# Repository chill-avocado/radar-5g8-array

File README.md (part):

# 5.8 GHz 2×2 MIMO radar array for a USRP B210

Two printed antenna boards — one transmit, one receive — at 5.8 GHz, each
carrying two circularly polarised patch elements.  Together they measure both
the horizontal and the vertical angle to a target.  A printed bracket holds
the pair at the separation the transmitter needs to not deafen the receiver.

Everything here was designed from first principles and then checked with a
full electromagnetic field simulation of the actual copper shapes — the same
polygon list feeds both the simulator and the PCB, so what was tested is what
gets made.

---

## What the boards do

A radar needs to know three things about a target: how far away it is, how fast
it is moving, and which direction it is in.  Distance and speed come from the
radio.  Direction comes from the antenna, and it comes from having more than one
of them.

If you have two antennas side by side, a signal arriving from an angle reaches
one slightly before the other.  That tiny delay tells you the angle.  Two
antennas side by side give you the *horizontal* angle.  Two stacked vertically
give you the *vertical* angle.

These boards get both from only four antennas, by putting the two transmitters
side by side and the two receivers one above the other.  Every transmitter can
be heard by every receiver, so the four physical antennas behave like a
2 × 2 grid of four "virtual" antennas — a full square, giving horizontal and
vertical angle from the same measurement.  That is what MIMO buys you: four
antennas doing the work of a larger array.

The spacing between each pair is 25.844 mm, exactly half a wavelength at
5.8 GHz.  Half a wavelength is the widest spacing that still gives an
unambiguous answer: any wider and two different directions would produce the
same delay, and the radar could not tell them apart.

### Why the transmit and receive antennas spin opposite ways

Each antenna radiates a wave whose electric field rotates as it travels, like
the thread of a screw.  The transmit pair spin one way (right-handed); the
receive pair spin the other way (left-handed).

This is not decoration.  It does two useful jobs at once:

- **It rejects the transmitter's own signal.**  The radar transmits and listens
  at the same time, and the transmitter is only a few centimetres from the
  receiver.  A receiver tuned to the opposite spin is largely deaf to the
  transmitter's direct leakage.
- **It still hears the target.**  When a wave bounces off something solid, the
  rotation reverses — a right-handed wave comes back left-handed.  So the
  receiver is deaf to the leakage but wide open to the echo.

---

## The two boards

### Why two boards, not one

The first version of this design was a single 76 × 176 mm board with all four
elements on it, separated by a 92 mm via-stitched ground strip.  Two openEMS
runs showed why that was the wrong answer:

- Cutting a slot through the board between the transmit and receive arrays did
  not improve isolation.  It made it **1.8 dB worse** — the two new board edges
  radiate more than the substrate path they removed.
- The substrate coupling was never the dominant route at that spacing.  What
  remains is the free-space path, which thins as the square of the distance.

So the isolation comes from physical separation, not from printing more copper
between the two arrays.  Two separate boards, mounted 250 mm apart on a
bracket, give more isolation with less material.

### Material: ZYF300CA-P PTFE

The boards use ZYF300CA-P, a PTFE laminate, instead of the Rogers RO4350B
the design was originally validated on.

- **Half the dielectric loss** — tan δ = 0.0018, against 0.0037 for RO4350B.
  On a radar that counts twice, once going out and once coming back.
- **Lower permittivity** — εr = 3.0, against 3.66.  Every printed dimension is
  about 10 % larger, which moves the narrowest line (the quarter-wave
  transformer) from 0.26 mm to 0.34 mm — a more comfortable etch.  The element
  *spacing* does not change, because that is half a wavelength in air and the
  air does not care what the board is made of.
- **Immersion silver, not ENIG.**  At 5.8 GHz the current only reaches 0.87 µm
  into the metal.  ENIG's 3 µm of nickel carries all of it — 2.7 times the
  resistance of copper, costing 4.3 % of range.  Silver's tarnish is a
  semiconductor and carries no current at all: a board gone black measures the
  same as a fresh one.

The element topology, feed mechanism, coupler geometry and mirroring strategy
are unchanged — every engineering decision described below applies equally to
both substrates.  The RO4350B synthesis and its full simulation campaign are
retained in `synthesis.json` and the `sim/` results as the verified design
reference.

### Board dimensions

Each board carries two elements at λ/2 spacing.  Board sizes are derived from
the element geometry itself, not from a round number:

| board | size | area |
|---|---|---|
| Transmit (azimuth) | 71.3 × 47.2 mm | 3 370 mm² |
| Receive (elevation) | 47.2 × 71.3 mm | 3 370 mm² |

Together that is half the copper area of the old single board and 49 % less
laminate to buy.

---

## Verified performance (RO4350B simulation campaign)

Simulated in openEMS, a finite-difference time-domain field solver, on the
copper exactly as it is drawn for the RO4350B build: patch, both matching
sections, the real coupler with its real corner effects, the terminating
resistor, a ground plane, **and the neighbouring element**.

That last point matters more than anything else here.  An antenna measured on
its own is not the antenna you get.  At half-wave spacing the neighbour is
25.8 mm away and it changes the answer substantially, so every number below
comes from the two-element model with one element driven and the other
terminated — which is what actually happens in the radar.

Both runs were taken to the -40 dB energy criterion.

**At 5.800 GHz**

| | element 1 (TX1, RX1) | element 2 (TX2, RX2) |
|---|---|---|
| Input match | **-20.6 dB** | **-14.5 dB** |
| Leakage into the neighbour | **-20.4 dB** | **-20.7 dB** |
| Polarisation purity (axial ratio) | **2.8 dB** | **3.2 dB** |
| Rejection of the wrong spin | **16 dB** | **15 dB** |
| Directivity | 5.9 dBi | 5.9 dBi |
| Transmit-to-receive separation | 92.1 mm (1.78 wavelengths) | |
| Worst transmit-to-receive leakage | **-40.3 dB**, measured on the whole board | |

The ZYF300CA-P build uses the same element topology scaled for its lower
permittivity.  Simulation of the ZYF pair in the array gave worst axial ratio
3.35 dB and worst match -10.7 dB — consistent with the RO4350B results and
within the same physics.  The lower loss tangent is expected to improve, not
degrade, the figures.

### Read the polarisation figure honestly

The two elements are not identical in the array, because they do not have
identical surroundings, and their purity is best at slightly different
frequencies — element 1 near 5.81 GHz, element 2 near 5.86 GHz.

| frequency | 5.70 | 5.74 | 5.78 | 5.80 | 5.82 | 5.86 | 5.90 GHz |
|---|---|---|---|---|---|---|---|
| element 1 | 5.4 | 4.4 | 3.2 | 2.8 | 2.8 | 3.9 | 5.8 dB |
| element 2 | 7.2 | 5.8 | 4.0 | 3.2 | 2.4 | 1.5 | 2.2 dB |

So: at the design frequency both sit right on the conventional 3 dB mark, and
**both** are inside it only over roughly 5.81–5.83 GHz.  Across the wider ISM
band the purity ranges from about 1.5 dB to 7 dB depending on element and
frequency.  Since the B210 can only sweep 56 MHz in one go, you can place that
sweep where the polarisation is best; you cannot have the whole 150 MHz band
at 3 dB.

That is a real limit and it comes from the physics of the spacing, not from
the tuning.  A single element on its own reaches 0.7 dB.  Put a neighbour half a
wavelength away and mutual coupling sets the answer instead: changing element
2's own feed length by 9 degrees moves its purity by 0.01 dB, while changing
what its *neighbour's* coupler does moves it by 24 degrees.  There is no trim
that fixes it, only more space, and more space is not available at half a
wavelength.

Practically, 3 dB purity gives about 15 dB of rejection of the wrong spin.
Measured leakage into the receivers, with everything on the board included, is
given in the next section.

### Transmit-to-receive isolation, measured on the single board

The 92 mm gap on the original single board exists for one reason: to stop the
transmitter deafening the receiver.  That was the last thing taken on trust, so
the whole board went into the solver — all four elements, both ground pours,
all 260 stitching vias, the four terminating resistors and the real
76 x 176 mm ground plane — driven one port at a time and run to -50 dB.

| | into RX1 | into RX2 | into the other transmitter |
|---|---|---|---|
| transmitting on TX1 | **-54.3 dB** | **-45.5 dB** | -21.8 dB |
| transmitting on TX2 | **-56.4 dB** | **-46.4 dB** | -21.6 dB |
| worst anywhere in the ISM band | -48.2 dB | **-41.1 dB** | -21.8 dB |

The model checks itself: transmit-to-transmit coupling comes out at -21.78 dB
one way and -21.62 dB the other, and reciprocity says those must be equal.
0.16 dB apart is a good sign the numbers are real.

**Worst total leakage into the receivers is -40.3 dB across the band.**  With
the B210 transmitting +10 dBm that is **-30.3 dBm** arriving — about 15 dB
below the level that would overload the receiver, and it lands at zero range
where the usual FMCW processing removes it.  That is better than the 30 to
35 dB the hand estimate predicted.

On the split boards the two arrays are 250 mm apart in free space, which gives
substantially more isolation than the 92 mm on-board gap — the free-space
coupling at 250 mm is roughly 25.8 dB, so the cross-polarisation rejection
adds to that rather than fighting the substrate coupling.

### The connector launch, measured

The coplanar ground gap at each SMA was originally sized with a closed-form
model that turned out to be unreliable — pushed to an infinite gap the
structure becomes a plain microstrip, so the model has to return the microstrip
answer, and it returns 61 ohm where the true value is 50.

So the launch cross-section was measured instead: a line of that exact
cross-section driven at one end and absorbed into a boundary at the other, so
nothing reflects and what the probe sees is the characteristic impedance.  Run
with the coplanar grounds deleted it returns 50.89 ohm against a true 50.00,
which is the check that the method itself is sound.

| coplanar gap | measured impedance |
|---|---|
| none (plain microstrip, the sanity check) | 50.89 ohm |
| **0.891 mm — RO4350B build** | **47.86 ohm** |
| 1.5 mm | 49.01 ohm |
| 2.5 mm | 49.46 ohm |
| 4.0 mm | 49.58 ohm |

The RO4350B board's 0.891 mm gap is **47.9 ohm**, not the 42 to 46 ohm the
broken model implied.  Over the 4.3 mm launch that is a **-29 dB** reflection.
The ZYF300CA-P build rescales the gap to 0.978 mm to match the wider 50 Ω
line on that substrate.  `design/rfmath.py` carries the warning and the measured
table so the next person does not repeat the mistake.

### What is still not simulated

The connector itself.  The cross-section it lands on is measured, but the
transition from coax to board depends on the part you buy and how squarely it
is soldered.  Expect the bench return loss to be set by that, not by the
antenna.

## The engineering decisions, and why

### Material history

The design was validated on **Rogers RO4350B 0.762 mm**, a controlled
RF laminate.  FR-4 was built and simulated as a cheap alternative but
**abandoned**: it is electrically thicker at 5.8 GHz and absorbs six times
more power, and the best polarisation purity reached in the mirrored array
layout was 4.8 dB axial ratio with a -4.7 dB input match — against 2.8 dB
and -20.6 dB for Rogers.  FR-4 at 5.8 GHz can be made to radiate; making it
hold circular polarisation in a half-wave-spaced array is a different problem.

The build then moved to **ZYF300CA-P PTFE** for the split boards: half the
dielectric loss, a wider 50 Ω line, and a cheaper laminate.  The Rogers
synthesis and simulation campaign are kept in `synthesis.json` as the verified
reference.  The generator still carries the FR-4 material model in
`synthesis.json` if you ever want to pick it up.

### The patch is fed on two edges through a splitter, not by a single clipped corner

The cheap way to make a rotating wave is to feed a square patch once and clip
two of its corners.  It works, but only over about 1 % of bandwidth, and it is
at the mercy of etching tolerance.

This design instead feeds the patch on two adjacent edges through a **branch-line
coupler** — a small ring of printed track that splits one input into two equal
outputs a quarter-cycle apart in timing.  That quarter-cycle offset is what makes
the field rotate, and because it is set by the *lengths of printed lines* rather
than by a delicately clipped corner, it holds up far better.

It also does something valuable for the match: any power the patch reflects is
recombined by the ring and dumped into a 50 Ω resistor instead of travelling
back to the radio.  That is why the input match holds below −10 dB from
5.715 to 5.890 GHz -- 175 MHz, measured on the final tuning -- while the
patch itself is far narrower than that.

### Things the simulation found that the textbook formulas got wrong

These are worth recording, because each one would have produced a dead board:

- **The patch edge impedance is 311 Ω, not the 587 Ω the standard model
  predicts.**  The textbook figure would have called for a 0.025 mm-wide
  matching line — thinner than any fab can etch.  An exact match to 311 ohm
  still wants 124.7 ohm, which is a 0.16 mm line; the board uses 110 ohm on a
  comfortable 0.34 mm line instead and lets the coupler dump the residual
  into the terminating resistors: measured 5.6 % at band centre and 30.3 % at
  5.725 GHz, which is why those parts are 1 W 0805s and not 0402s.  That is the mechanism working as
  designed, not a rounding error.
- **A deep notch cut into the patch to feed it destroys the polarisation.**
  Cutting a 2.7 mm slot dropped the isolation between the two feed points from
  −37.6 dB to −4.5 dB, because the slot sits exactly where the other mode's
  current peaks.  The patch is therefore left whole and the matching is done in
  the feed line.
- **The coupler ring behaves about 10 % shorter than its drawn length**,
  because each corner is a junction whose electrical reference sits inside it.
  Left uncorrected the ring was centred at 6.38 GHz instead of 5.8 GHz.
- **A neighbour at half-wave spacing is not a small perturbation.**  It moved
  the polarisation purity from 0.7 dB to between 3 and 7 dB depending on which
  element, and it is why the second element of each pair is mirrored.  It also
  overrides the element's own tuning: the coupler unbalance that is right for
  a lone element is not right for one with a neighbour.
- **The feed network, sitting on one side of the patch, loads its two
  resonances unequally.**  That knocked the polarisation purity of a lone
  element to 3.6 dB.  The fix is a coupler that is deliberately *unequal* — it
  sends 2.8 dB more power to the lightly loaded side, which cancels the
  imbalance and takes a lone element to 0.7 dB.

### Board layout

- Two elements at λ/2 spacing on each board.
- Transmit pair side by side (azimuth), cables leaving one edge.
  Receive pair stacked (elevation), cables leaving a perpendicular edge.
  The two sets of cables therefore leave at right angles to each other and
  neither passes in front of a radiating face.
- Solder mask is deliberately omitted over the antennas and the connector
  transitions.  Mask over a patch shifts its frequency and adds loss.
- Rounded 3 mm corners, because a square corner on a 0.76 mm laminate is
  the first thing to chip.

---

## What else is on the boards

### Receive limiter sites (D1, D2) — fitted by you, not by me

The drones this radar is built to find carry 5.8 GHz video transmitters, on
our own frequency, at up to a watt or two.  That is a bigger hazard to the
receiver than our own transmitter:

| range | 25 mW drone | 1 W drone | 2 W drone |
|---|---|---|---|
| 0.3 m | -15.4 dBm | **+0.6** | **+3.6** |
| 1 m | -25.8 | **-9.8** | -6.8 |
| 3 m | -35.4 | -19.4 | -16.4 |

The B210 compresses at about -15 dBm and its absolute maximum is 0 dBm.  A
watt-class drone at a metre already overloads it; at a third of a metre it is
into damage territory.  Our own transmitter, by contrast, only leaks -30.3 dBm.

So each receive line carries an **empty** shunt site, as close to the connector
as the launch will allow.  Simulated both ways:

| limiter fitted | return loss | insertion loss |
|---|---|---|
| **none, as shipped** | **-22.1 dB** | **0.09 dB** |
| 0.10 pF diode | -13.8 dB | 0.26 dB |
| 0.20 pF diode | -8.1 dB | 0.82 dB |
| 0.40 pF diode | -0.8 dB | 8.4 dB |

Empty, the site is invisible.  Fitted, everything depends on the diode's
off-state capacitance: **0.10 pF or less, or do not fit it**.  At 0.4 pF the
diode simply shorts the line.  If you need more protection margin than a 0.1 pF
part gives, use an in-line coaxial limiter instead — you lose nothing on these
boards by leaving the sites empty.

### Assembly and mechanical data

- **JLCPCB pick-and-place and bill of materials** with LCSC part numbers, so
  the terminations can be machine-fitted.
- **A mechanical DXF** of the outline, hole pattern, connector envelopes,
  patch apertures and phase-centre marks, so a bracket or radome can be cut to
  match the board without measuring anything.
- **`array_report.json`** — element positions, virtual-array geometry, derived
  beam figures and the measured performance, in a form the processing chain
  can read directly instead of someone typing coordinates off a drawing.

### Alignment and assembly

- **Fiducials** (1 mm copper in a 2 mm mask window) for optical
  placement, tied to ground through a thin neck so nothing floats.
- **Orientation legend** on the back: which array is which, which way each
  spins as seen from the radiating face, and which face is boresight.
- **Element phase-centre coordinates** are tabulated on the fabrication
  drawing, so the numbers can go straight into the beamforming code without
  anyone measuring a board.

---

## Mechanical carrier

A patch antenna does not radiate off the patch alone.  It radiates off the
patch working against the metal beneath it, and that metal has to keep going
for roughly half a wavelength past the patch or the field runs off the edge,
wraps round the back, and comes out the other side turned the wrong way.
Measured on this exact element: 6 mm of laminate past the patch gives 7.61 dB
axial ratio; 25 mm of metal gives 2.74 dB.

The boards are deliberately shrunk to save money on laminate, with the
understanding that a bracket supplies the rest of the ground.  **It is not an
accessory.**

Each board sits on a **1.5 mm aluminium plate** sized to give 25 mm of metal
past every patch edge.  The board's whole back face is ground copper and it
clamps flat against the plate, which is a far better bond than any bolt.

The two plates sit in **3D-printed trays** joined by a bar with a **lap joint
on a 10 mm pitch**, so the transmit-to-receive separation is settable from
220 to 280 mm.  250 mm is the design point.  A shelf bracket is included for
wall mounting.

```
mech/   carrier.py          generates the bracket and plates
        carrier.scad         OpenSCAD source (parametric)
        half_transmit.stl    3D-printable tray, transmit side
        half_receive.stl     3D-printable tray, receive side
        shelf.stl            wall-mount shelf bracket
        plate_transmit.dxf   laser-cut backing plate, transmit
        plate_receive.dxf    laser-cut backing plate, receive
```

The plate stops short of the connector edge — two notches — because the
coaxial connectors clamp round the board and need their lower jaw free.

---

## Active front-end boards

The passive antenna boards are the verified, build-now parts.  But a passive
board with the B210 alone can only see a small drone at about **173 metres**
(0.01 m² target, 100 ms integration, 13 dB threshold).  For longer range, the
system needs amplifiers.

Two active boards exist as complete, manufacturable designs with KiCad
projects, Gerbers, BOMs and placement files.  They have **not** been through
the same element-by-element simulation verification as the antenna boards — the
polygon-to-simulator integrity guarantee does not yet apply to them.

### LNA board (receive amplifier)

A two-channel low-noise preamplifier on 4-layer FR-4.  Each channel carries:

- **A limiter** with quarter-wave impedance transformers that drop the local
  line to 27 Ω, pushing the parasitic low-pass corner from the diode's
  off-state capacitance up to 12 GHz — well above the band, so the limiter is
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
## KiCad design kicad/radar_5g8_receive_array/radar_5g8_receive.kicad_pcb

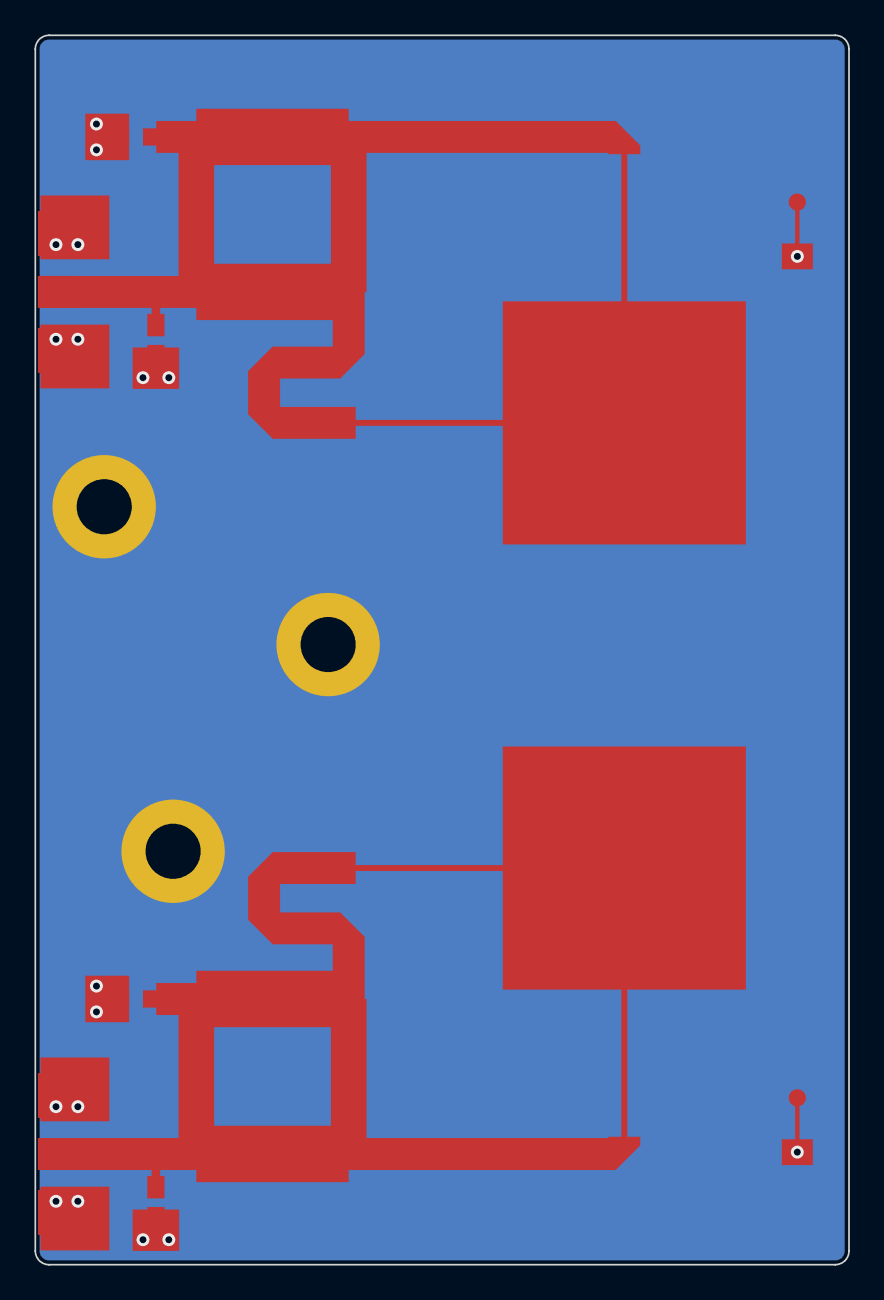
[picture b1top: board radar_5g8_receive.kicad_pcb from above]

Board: 2 copper layers, 47.2 x 71.4 mm, 9 parts (0 on the bottom side), 3 nets, no tracks yet.

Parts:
D1, D2: DNF - limiter site; D_0805_Limiter
H1, H2, H3: M3; MountingHole_M3
R3, R4: 50R; R_0805_1W_50R
RX1, RX2: SMA-EDGE-50R; SMA_EndLaunch_50R_LeftEdge

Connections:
GND: D1.2, D2.2, H1.1, H2.1, H3.1, R3.2, R4.2, RX1.2, RX1.3, RX2.2, RX2.3
RX1: D1.1, R3.1, RX1.1
RX2: D2.1, R4.1, RX2.1

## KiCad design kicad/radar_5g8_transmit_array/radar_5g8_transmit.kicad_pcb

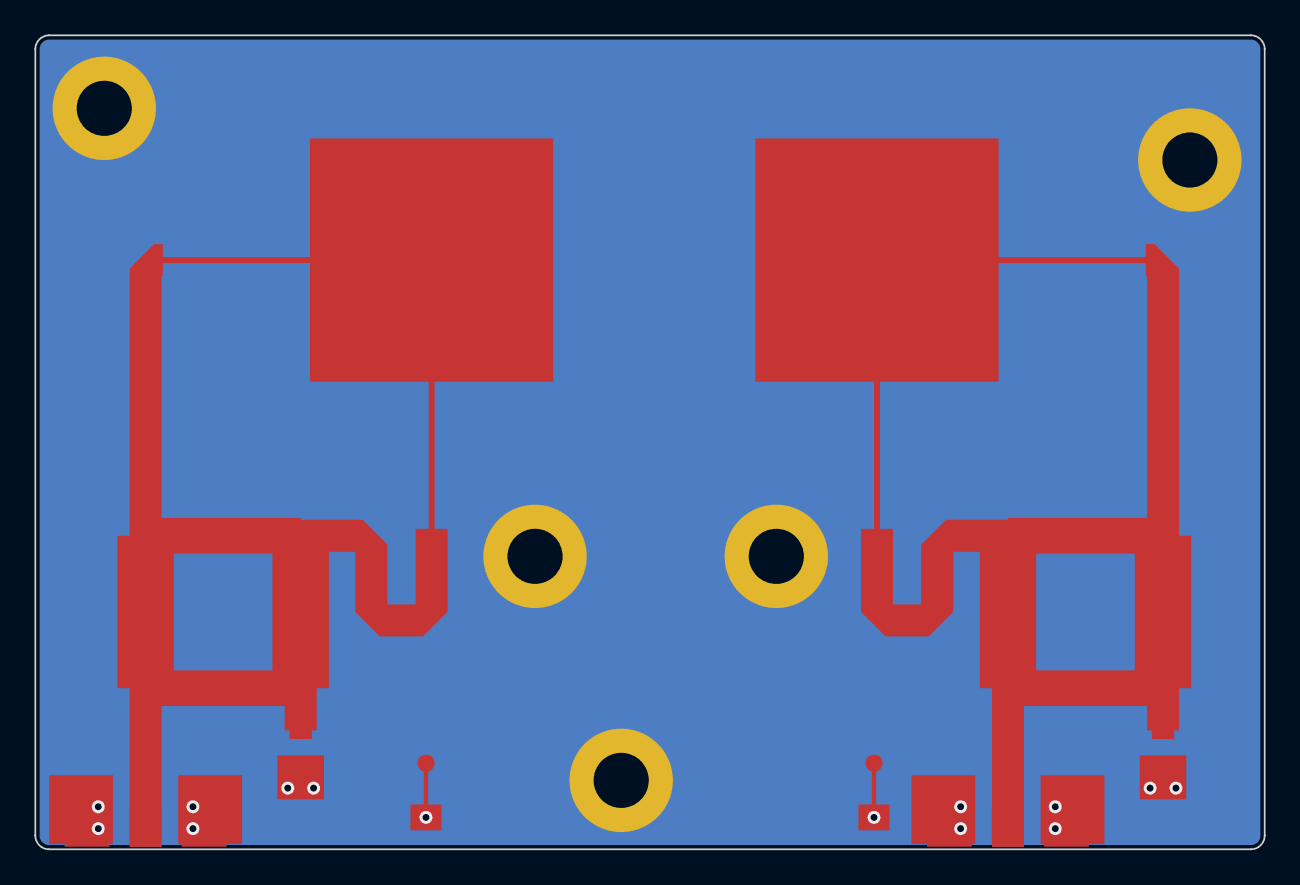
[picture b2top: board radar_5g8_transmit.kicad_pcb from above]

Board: 2 copper layers, 71.3 x 47.2 mm, 9 parts (0 on the bottom side), 3 nets, no tracks yet.

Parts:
H1, H2, H3, H4, H5: M3; MountingHole_M3
R1, R2: 50R; R_0805_1W_50R
TX1, TX2: SMA-EDGE-50R; SMA_EndLaunch_50R_BottomEdge

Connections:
GND: H1.1, H2.1, H3.1, H4.1, H5.1, R1.2, R2.2, TX1.2, TX1.3, TX2.2, TX2.3
TX1: R1.1, TX1.1
TX2: R2.1, TX2.1

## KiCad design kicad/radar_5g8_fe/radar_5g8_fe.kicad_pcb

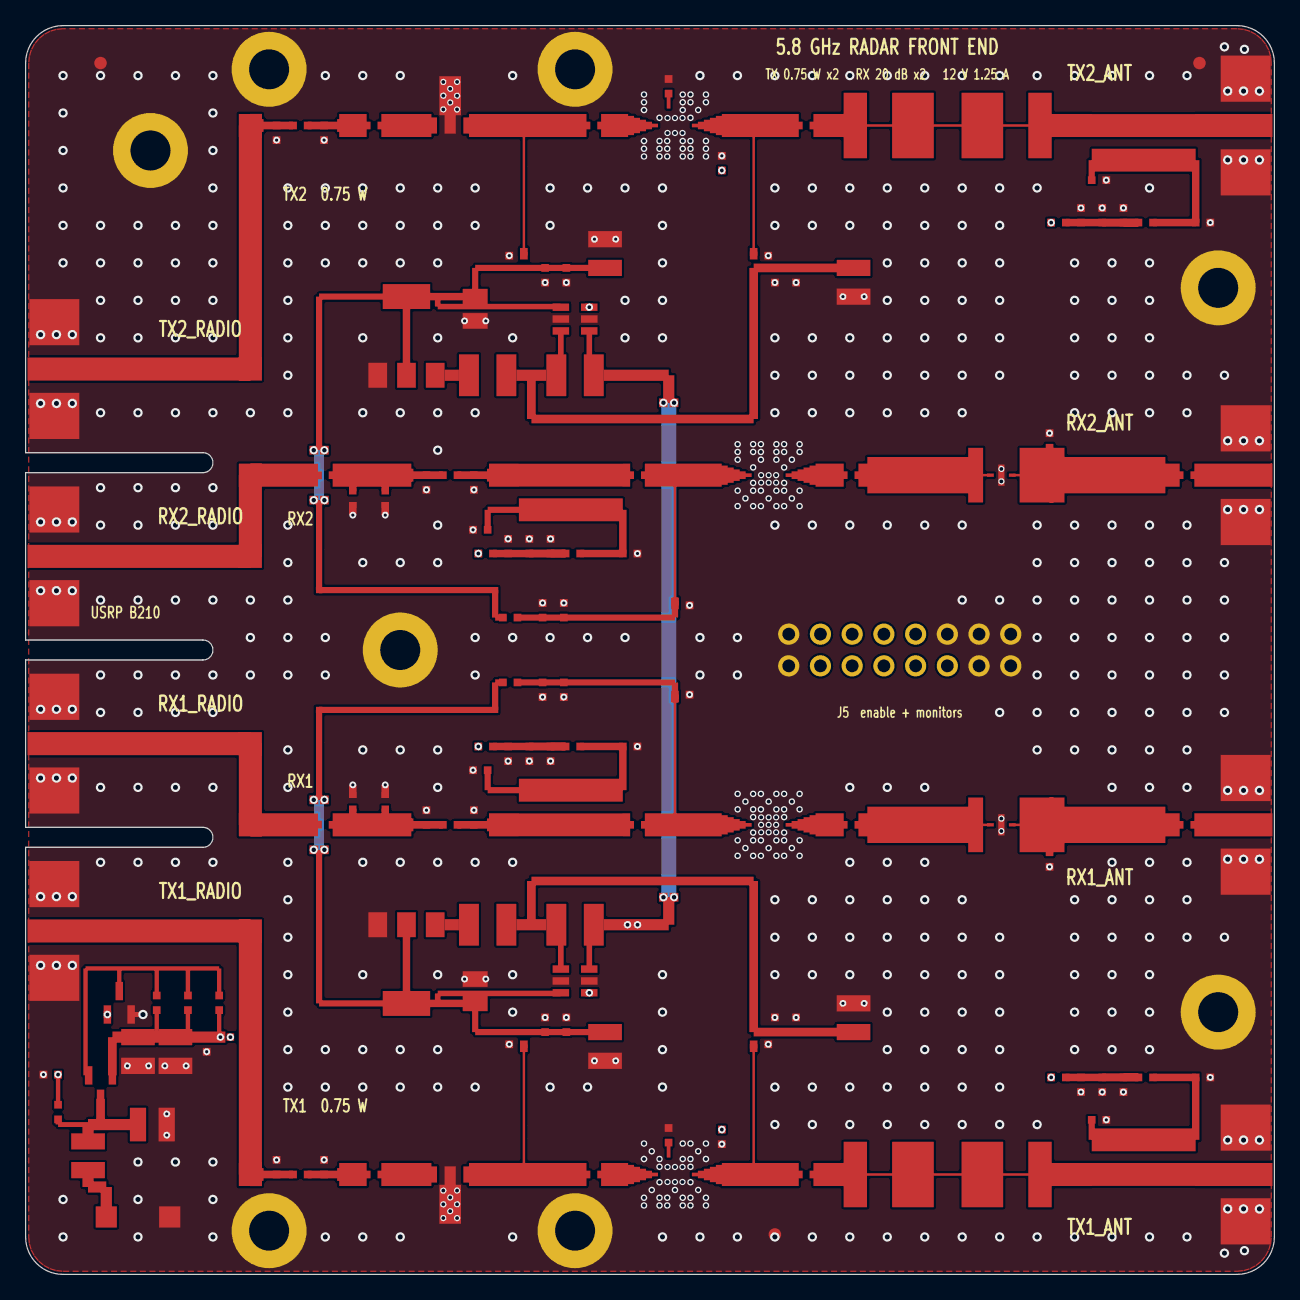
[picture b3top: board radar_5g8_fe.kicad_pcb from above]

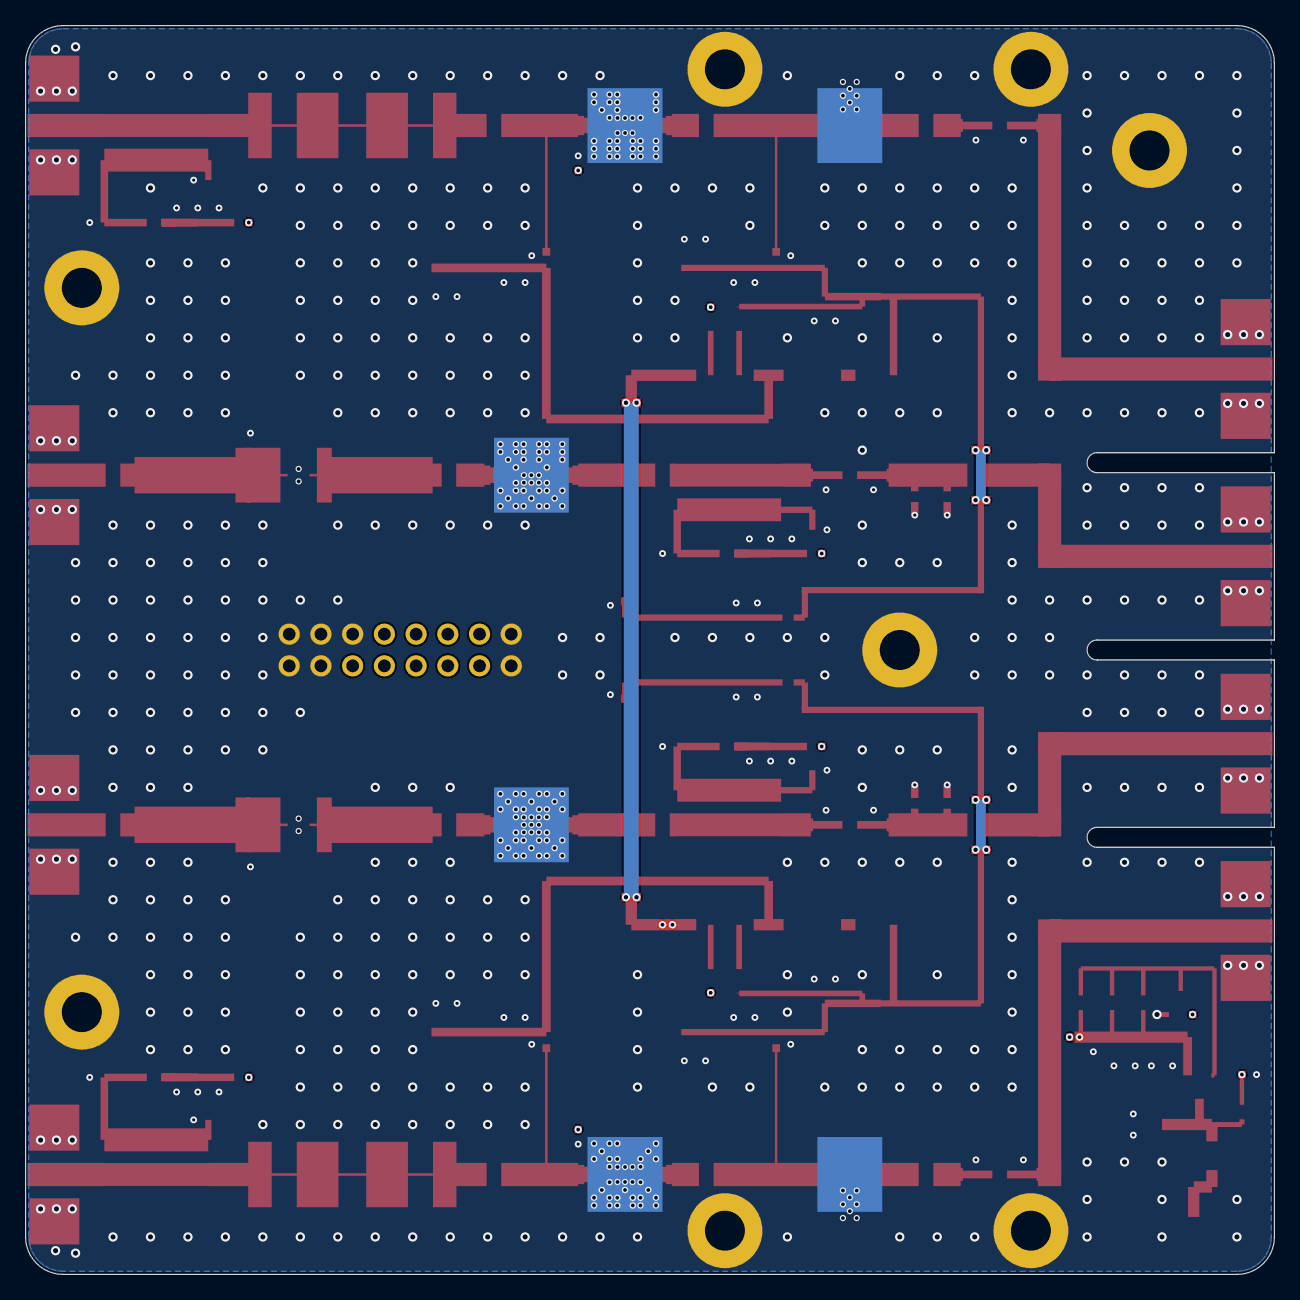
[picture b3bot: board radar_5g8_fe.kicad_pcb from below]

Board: 4 copper layers, 100.0 x 100.0 mm, 133 parts (6 on the bottom side), 48 nets, no tracks yet.

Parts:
C1, C214: 100n
C29, C212: 22u
CA1, CA2, CA3, CA81, CA91: 1n
CA5, CA83, CA93: 10u
CA80, CA90: 100p
CA82, CA92: 100n
CAD0: 100p
CAD2: 10n
CB1, CB2, CB3, CB81, CB91: 1n
CB5, CB83, CB93: 10u
CB80, CB90: 100p
CB82, CB92: 100n
CBD0: 100p
CBD2: 10n
CC1, CC2, CC3, CC4, CC80: 100p
CC81: 1n
CC82: 100n
CCD0: 100p
CCD2: 10n
CD1, CD2, CD3, CD4, CD80: 100p
CD81: 1n
CD82: 100n
CDD0: 100p
CDD2: 10n
D5: SMBJ15A
D6: 10V
DA1: SMS7630
DB1: SMS7630
DC1: SMS7630
DCC1, DCC2: SMS7630-079LF
DCL: SMP1330-085LF
DD1: SMS7630
DDC1, DDC2: SMS7630-079LF
DDL: SMP1330-085LF
F1: MF-MSMF150
FBC: 600R
FBD: 600R
FID6_97, FID60_3, FID94_97: (no value)
H10_90, H19_3, H19_96, H30_50, H44_3, H44_96, H95_21, H95_79: M3
J1: (no value)
J5: 8x2 2.54 mm header
LDCL: 10n
LDDL: 10n
Q3: AO3401A
Q4: 2N7002
R1: 100k
R2: (no value)
R3: 47k
RAD1: 10k
RAF: 51R
RAI: (no value)
RAO: 1k
RAP1, RAP3: 150R
RAP2: 36R
RAS: (no value)
RAT: 51R
RAV: (no value)
RBD1: 10k
RBF: 51R
RBI: (no value)
RBO: 1k
RBP1, RBP3: 150R
RBP2: 36R
RBS: (no value)
RBT: 51R
RBV: (no value)
RCD1: 10k
RCF: 51R
RCO: 1k
RCP1, RCP3: 120R
RCP2: 51R
RCT: 51R
RDD1: 10k
RDF: 51R
RDO: 1k
RDP1, RDP3: 120R
RDP2: 51R
RDT: 51R
RTA: 10k NTC
RTB: 10k NTC
TP1, TP2, TP3, TP4, TP5, TP6: thermal face
UA1: PHA-1H+
UA3: AMS1117-5.0
UA4: INA181A2IDBVR
UB1: PHA-1H+
UB3: AMS1117-5.0
UB4: INA181A2IDBVR

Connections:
DETA: J5.14, RAO.1
DETB: J5.5, RBO.1
DETC: J5.11, RCO.1
DETD: J5.2, RDO.1
EN: J5.10, Q4.1, R2.2, R3.1
GND: C29.2, C212.2, C214.2, CA5.2, CA80.2, CA81.2, CA82.2, CA83.2, CA90.2, CA91.2, CA92.2, CA93.2, CAD0.2, CAD2.2, CB5.2, CB80.2, CB81.2, CB82.2, CB83.2, CB90.2, CB91.2, CB92.2, CB93.2, CBD0.2, CBD2.2, CC80.2, CC81.2, CC82.2, CCD0.2, CCD2.2, CD80.2, CD81.2, CD82.2, CDD0.2, CDD2.2, D5.2, DCC1.2, DCC2.1, DCL.2, DDC1.2, DDC2.1, DDL.2, FID6_97.1, FID60_3.1, FID94_97.1, H10_90.1, H19_3.1, H19_96.1, H30_50.1, H44_3.1, H44_96.1, H95_21.1, H95_79.1, J1.2, J5.1, J5.6, J5.7, J5.8, J5.9, J5.15, J5.16, LDCL.2, LDDL.2, Q4.2, R3.2, RAD1.2, RAF.2, RAI.2, RAP1.2, RAP3.2, RAT.2, RBD1.2, RBF.2, RBI.2, RBP1.2, RBP3.2, RBT.2, RCD1.2, RCF.2, RCP1.2, RCP3.2, RCT.2, RDD1.2, RDF.2, RDP1.2, RDP3.2, RDT.2, RTA.2, RTB.2, TP1.1, TP2.1, TP3.1, TP4.1, TP5.1, TP6.1, UA1.2, UA1.4, UA3.1, UA4.2, UA4.5, UB1.2, UB1.4, UB3.1, UB4.2, UB4.5
IMONA: J5.12, UA4.1
IMONB: J5.3, UB4.1
RX1_CPL: DC1.2, RCF.1, RCT.1
RX1_CPLM: CC3.1, RCP2.2, RCP3.1
RX1_DETV: CCD0.1, CCD2.1, DC1.1, RCD1.1, RCO.2
RX1_L: CC1.1, DCL.3, LDCL.1
RX1_LI: CC2.2, DCL.1
RX1_P: CC4.2, DCC1.1, DCC2.2, RCP1.1, RCP2.1
RX1_T: CC3.2, CC80.1, CC81.1, CC82.1, FBC.2
RX2_CPL: DD1.2, RDF.1, RDT.1
RX2_CPLM: CD3.1, RDP2.2, RDP3.1
RX2_DETV: CDD0.1, CDD2.1, DD1.1, RDD1.1, RDO.2
RX2_L: CD1.1, DDL.3, LDDL.1
RX2_LI: CD2.2, DDL.1
RX2_P: CD4.2, DDC1.1, DDC2.2, RDP1.1, RDP2.1
RX2_T: CD3.2, CD80.1, CD81.1, CD82.1, FBD.2
TEMPA: J5.13, RTA.1
TEMPB: J5.4, RTB.1
TX1_CPL: DA1.2, RAF.1, RAT.1
TX1_D: CA2.1, CA90.1, UA1.3
TX1_DETV: CAD0.1, CAD2.1, DA1.1, RAD1.1, RAO.2
TX1_DI: CA1.2, UA1.1
TX1_IN: RAP1.1, RAP2.1
TX1_P: CA1.1, RAP2.2, RAP3.1
TX1_PA: CA3.1, CA80.1
TX2_CPL: DB1.2, RBF.1, RBT.1
TX2_D: CB2.1, CB90.1, UB1.3
TX2_DETV: CBD0.1, CBD2.1, DB1.1, RBD1.1, RBO.2
TX2_DI: CB1.2, UB1.1
TX2_IN: RBP1.1, RBP2.1
TX2_P: CB1.1, RBP2.2, RBP3.1
TX2_PA: CB3.1, CB80.1
V5A: CA5.1, CA91.1, CA92.1, CA93.1, FBC.1, UA3.2, UA4.6
V5A_I: RAV.1, UA3.3
V5B: CB5.1, CB91.1, CB92.1, CB93.1, FBD.1, UB3.2, UB4.6
V5B_I: RBV.1, UB3.3
V12: C1.1, C29.1, C212.1, C214.1, D6.1, Q3.2, R1.1, RAS.2, RBS.2, UA4.3, UB4.3
V12A: CA81.1, CA82.1, CA83.1, RAS.1, RAV.2, UA4.4
V12B: CB81.1, CB82.1, CB83.1, RBS.1, RBV.2, UB4.4
V12G: C1.2, D6.2, Q3.1, Q4.3, R1.2
VF: D5.1, F1.2, Q3.3, R2.1
VIN: F1.1, J1.1

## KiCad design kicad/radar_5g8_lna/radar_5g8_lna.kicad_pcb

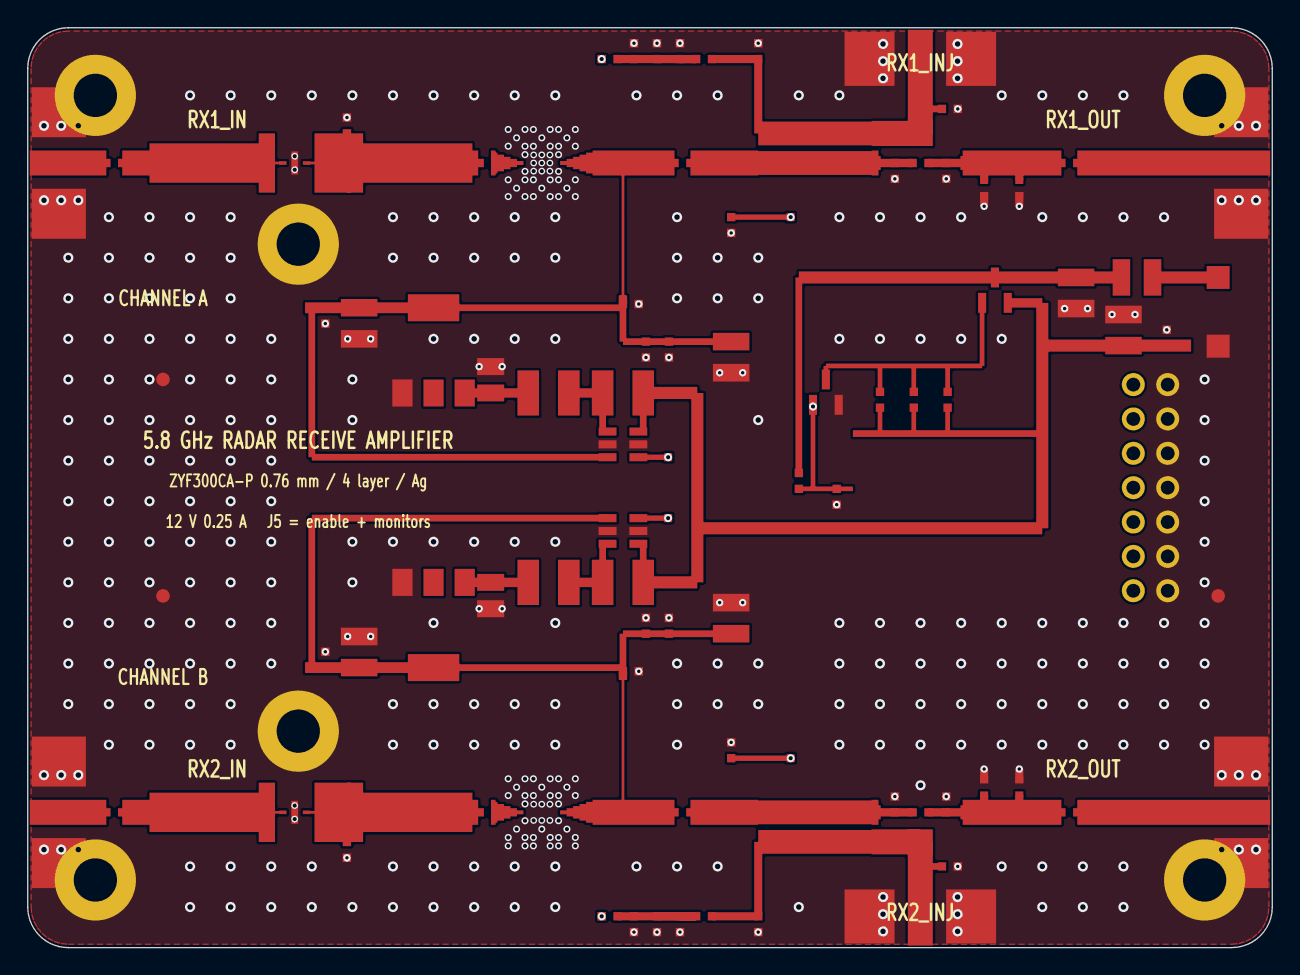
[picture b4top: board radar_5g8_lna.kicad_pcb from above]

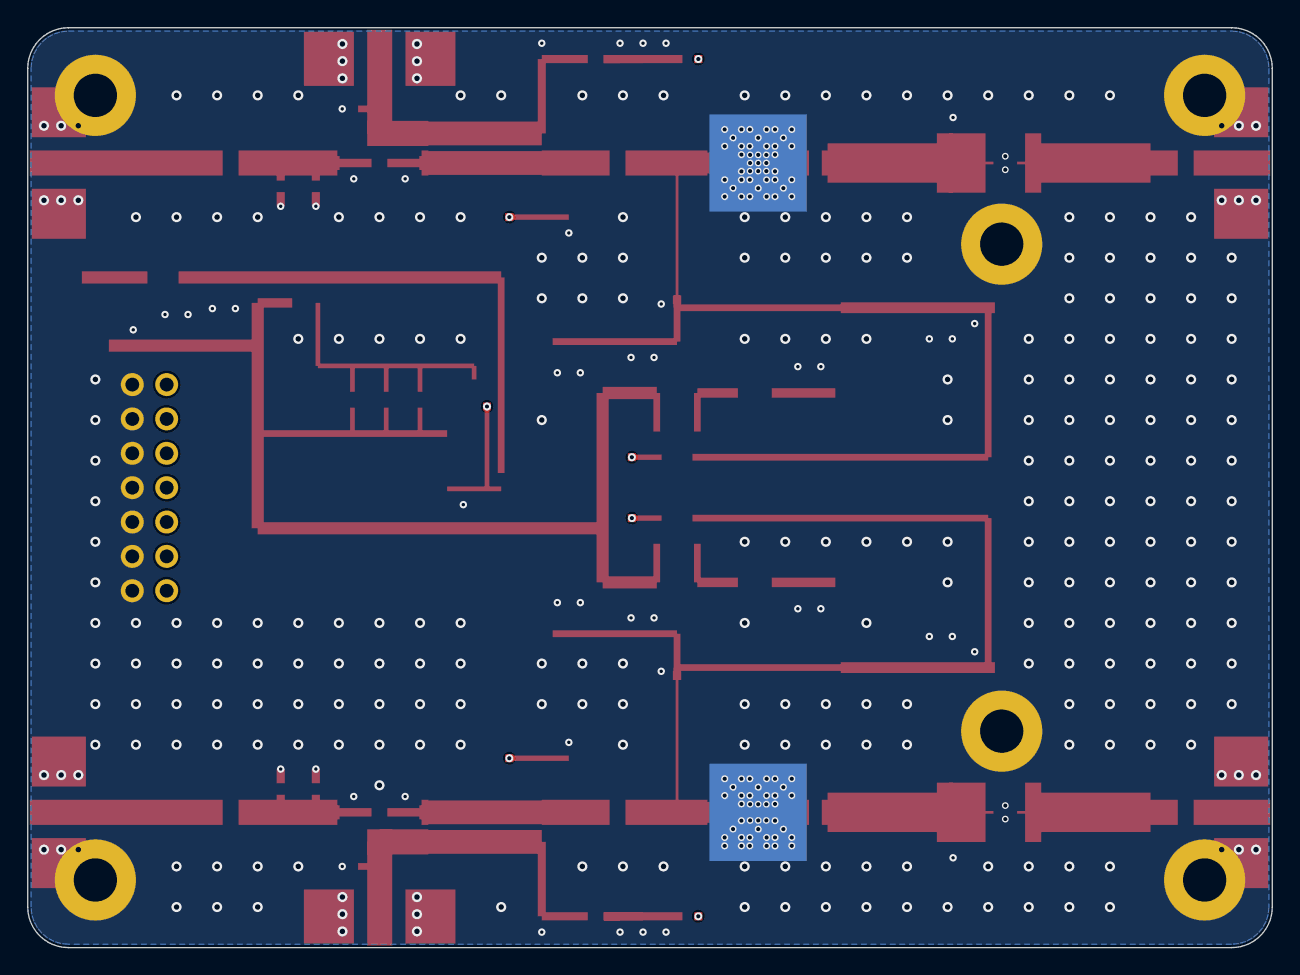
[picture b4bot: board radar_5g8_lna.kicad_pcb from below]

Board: 4 copper layers, 92.0 x 68.0 mm, 84 parts (2 on the bottom side), 30 nets, no tracks yet.

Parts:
C1, C21: 100n
C20: 22u
CA1, CA2, CA3, CA4, CA80: 100p
CA5, CA6, CA83: 10u
CA7, CA82: 100n
CA81: 1n
CAD0: 100p
CAD2: 10n
CB1, CB2, CB3, CB4, CB80: 100p
CB5, CB6, CB83: 10u
CB7, CB82: 100n
CB81: 1n
CBD0: 100p
CBD2: 10n
D5: SMBJ15A
D6: 10V
DA1: SMS7630
DAC1, DAC2: SMS7630-079LF
DAL: SMP1330-085LF
DB1: SMS7630
DBC1, DBC2: SMS7630-079LF
DBL: SMP1330-085LF
F1: MF-MSMF100
FID10_26, FID10_42, FID88_26: (no value)
H5_5, H5_63, H20_16, H20_52, H87_5, H87_63: M3
J1: (no value)
J5: 2x7 2.54 mm header
LDAL: 10n
LDBL: 10n
Q3: AO3401A
Q4: 2N7002
R1, R2: 100k
R3: 47k
RAD1: 10k
RAJ: 51R
RAO: 1k
RAP1, RAP3: 120R
RAP2: 51R
RAS: (no value)
RAT: 51R
RAV: (no value)
RBD1: 10k
RBJ: 51R
RBO: 1k
RBP1, RBP3: 120R
RBP2: 51R
RBS: (no value)
RBT: 51R
RBV: (no value)
RTA: 10k NTC
RTB: 10k NTC
TP1, TP2: thermal face
UA2: AMS1117-5.0
UA3: INA181A2IDBVR
UB2: AMS1117-5.0
UB3: INA181A2IDBVR

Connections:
DETA: J5.7, RAO.1
DETB: J5.11, RBO.1
EN: J5.1, Q4.1, R2.1, R3.1
GND: C20.2, C21.2, CA5.2, CA6.2, CA7.2, CA80.2, CA81.2, CA82.2, CA83.2, CAD0.2, CAD2.2, CB5.2, CB6.2, CB7.2, CB80.2, CB81.2, CB82.2, CB83.2, CBD0.2, CBD2.2, D5.2, DAC1.2, DAC2.1, DAL.2, DBC1.2, DBC2.1, DBL.2, FID10_26.1, FID10_42.1, FID88_26.1, H5_5.1, H5_63.1, H20_16.1, H20_52.1, H87_5.1, H87_63.1, J1.2, J5.2, J5.4, J5.6, J5.8, J5.10, J5.12, J5.14, LDAL.2, LDBL.2, Q4.2, R3.2, RAD1.2, RAJ.2, RAP1.2, RAP3.2, RAT.2, RBD1.2, RBJ.2, RBP1.2, RBP3.2, RBT.2, RTA.2, RTB.2, TP1.1, TP2.1, UA2.1, UA3.2, UA3.5, UB2.1, UB3.2, UB3.5
IMONA: J5.5, UA3.1
IMONB: J5.9, UB3.1
RX1_CPL: DA1.2, RAJ.1, RAT.1
RX1_CPLM: CA3.2, RAP1.1, RAP2.1
RX1_DETV: CAD0.1, CAD2.1, DA1.1, RAD1.1, RAO.2
RX1_L: CA1.2, DAL.1
RX1_LI: CA2.1, DAL.3, LDAL.1
RX1_P: CA4.1, DAC1.1, DAC2.2, RAP2.2, RAP3.1
RX1_T: CA3.1, CA6.1, CA7.1, CA80.1, CA81.1, CA82.1, CA83.1, UA2.2, UA3.6
RX2_CPL: DB1.2, RBJ.1, RBT.1
RX2_CPLM: CB3.2, RBP1.1, RBP2.1
RX2_DETV: CBD0.1, CBD2.1, DB1.1, RBD1.1, RBO.2
RX2_L: CB1.2, DBL.1
RX2_LI: CB2.1, DBL.3, LDBL.1
RX2_P: CB4.1, DBC1.1, DBC2.2, RBP2.2, RBP3.1
RX2_T: CB3.1, CB6.1, CB7.1, CB80.1, CB81.1, CB82.1, CB83.1, UB2.2, UB3.6
TEMPA: J5.3, RTA.1
TEMPB: J5.13, RTB.1
V5A_I: CA5.1, RAV.1, UA2.3
V5B_I: CB5.1, RBV.1, UB2.3
V12: C1.1, C20.1, C21.1, D6.1, Q3.2, R1.1, RAS.2, RBS.2, UA3.3, UB3.3
V12A: RAS.1, RAV.2, UA3.4
V12B: RBS.1, RBV.2, UB3.4
V12G: C1.2, D6.2, Q3.1, Q4.3, R1.2
VF: D5.1, F1.1, Q3.3, R2.2
VIN: F1.2, J1.1

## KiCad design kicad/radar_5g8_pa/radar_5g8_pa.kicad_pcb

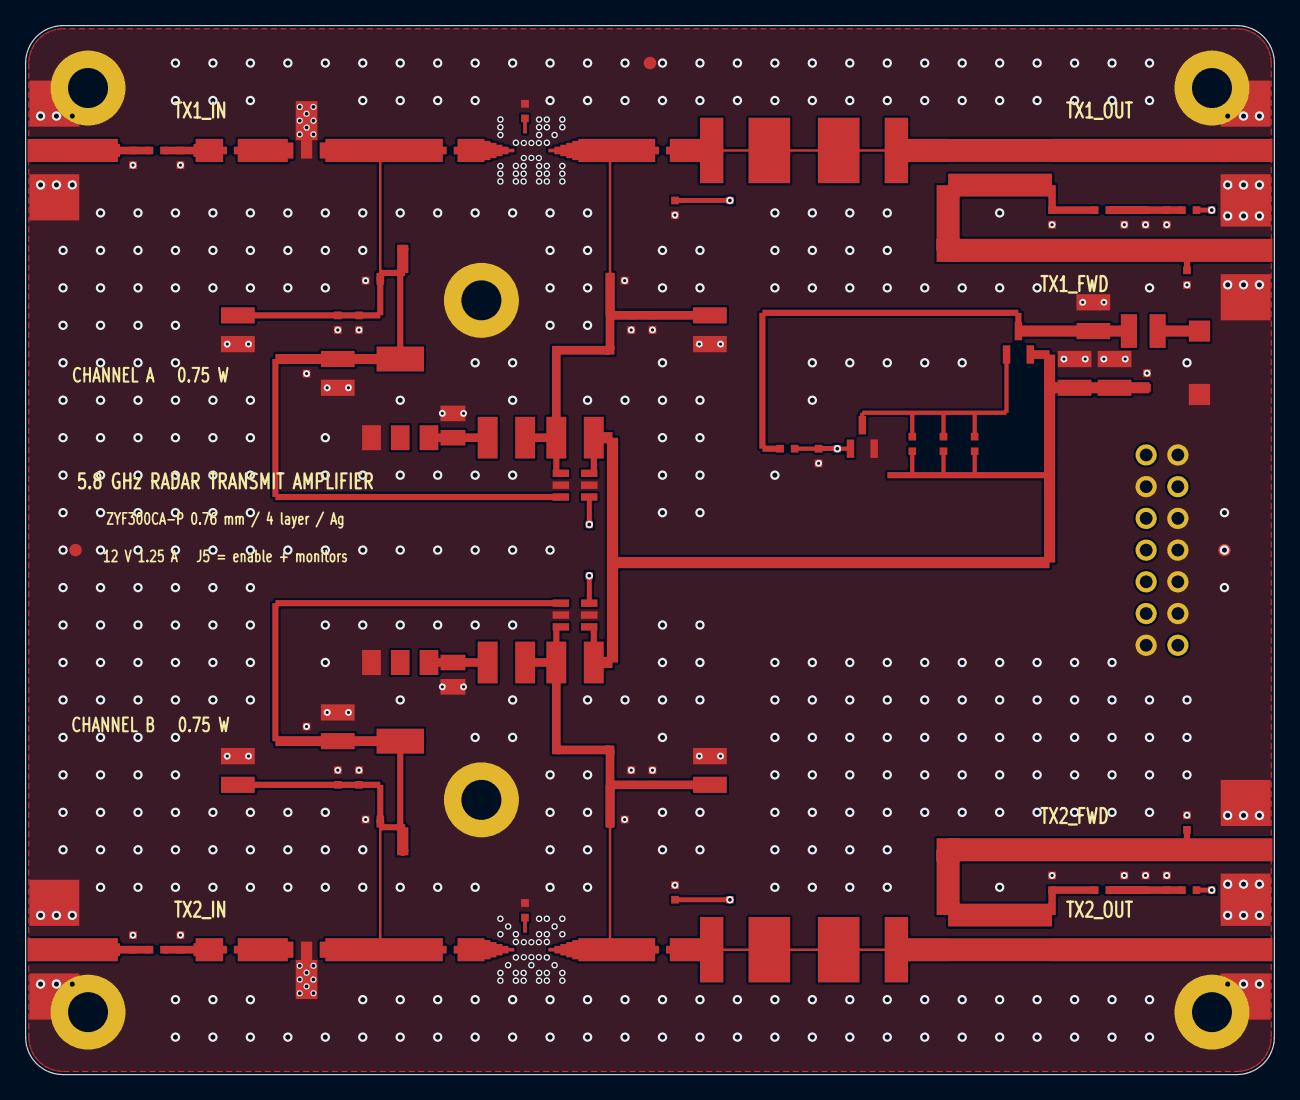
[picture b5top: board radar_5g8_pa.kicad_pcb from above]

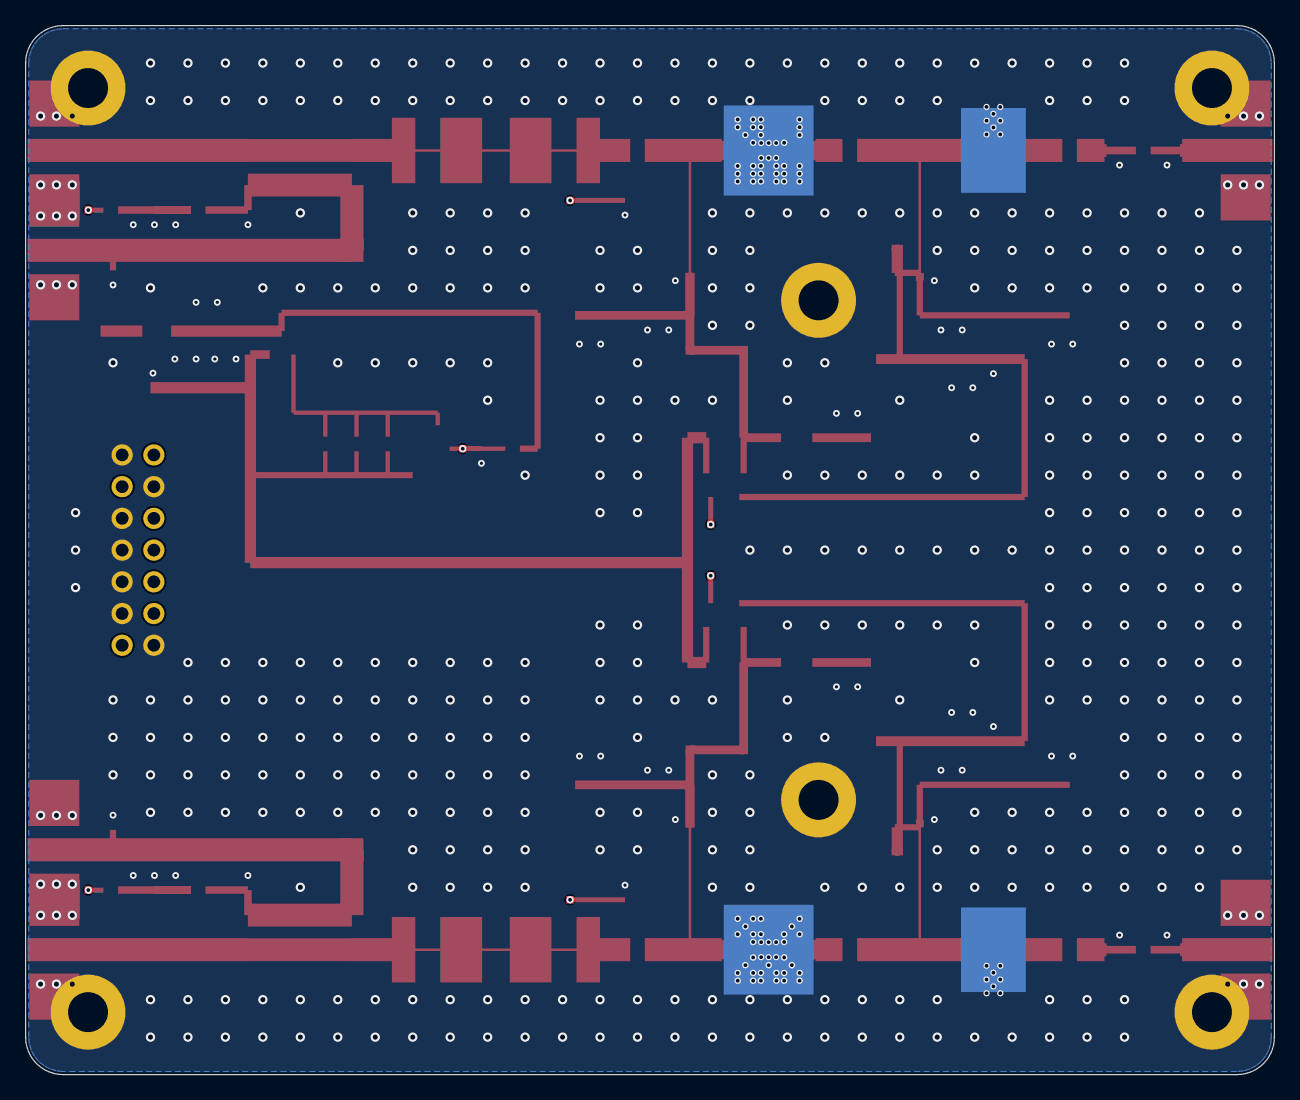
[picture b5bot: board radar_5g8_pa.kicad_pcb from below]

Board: 4 copper layers, 100.0 x 84.0 mm, 89 parts (4 on the bottom side), 28 nets, no tracks yet.

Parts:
C1, C22: 100n
C20, C21: 22u
CA1, CA2, CA3, CA81, CA91: 1n
CA5, CA6, CA83, CA93: 10u
CA7, CA82, CA92: 100n
CA80, CA90: 100p
CAD0: 100p
CAD2: 10n
CB1, CB2, CB3, CB81, CB91: 1n
CB5, CB6, CB83, CB93: 10u
CB7, CB82, CB92: 100n
CB80, CB90: 100p
CBD0: 100p
CBD2: 10n
D5: SMBJ15A
D6: 10V
DA1: SMS7630
DB1: SMS7630
F1: MF-MSMF150
FID4_42, FID50_81, FID96_42: (no value)
H5_5, H5_79, H36_22, H36_62, H95_5, H95_79: M3
J1: (no value)
J5: 2x7 2.54 mm header
Q3: AO3401A
Q4: 2N7002
R1, R2: 100k
R3: 47k
RAD1: 10k
RAF: 51R
RAI: (no value)
RAO: 1k
RAP1, RAP3: 150R
RAP2: 36R
RAS: (no value)
RAT: 51R
RAV: (no value)
RBD1: 10k
RBF: 51R
RBI: (no value)
RBO: 1k
RBP1, RBP3: 150R
RBP2: 36R
RBS: (no value)
RBT: 51R
RBV: (no value)
RTA: 10k NTC
RTB: 10k NTC
TP1, TP2, TP3, TP4: thermal face
UA1: PHA-1H+
UA3: AMS1117-5.0
UA4: INA181A2IDBVR
UB1: PHA-1H+
UB3: AMS1117-5.0
UB4: INA181A2IDBVR

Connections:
DETA: J5.4, RAO.2
DETB: J5.14, RBO.2
EN: J5.1, Q4.1, R2.2, R3.1
GND: C20.2, C21.2, C22.2, CA5.2, CA6.2, CA7.2, CA80.2, CA81.2, CA82.2, CA83.2, CA90.2, CA91.2, CA92.2, CA93.2, CAD0.2, CAD2.2, CB5.2, CB6.2, CB7.2, CB80.2, CB81.2, CB82.2, CB83.2, CB90.2, CB91.2, CB92.2, CB93.2, CBD0.2, CBD2.2, D5.2, FID4_42.1, FID50_81.1, FID96_42.1, H5_5.1, H5_79.1, H36_22.1, H36_62.1, H95_5.1, H95_79.1, J1.2, J5.2, J5.3, J5.6, J5.8, J5.10, J5.12, J5.13, Q4.2, R3.2, RAD1.2, RAF.2, RAI.2, RAP1.2, RAP3.2, RAT.2, RBD1.2, RBF.2, RBI.2, RBP1.2, RBP3.2, RBT.2, RTA.2, RTB.2, TP1.1, TP2.1, TP3.1, TP4.1, UA1.2, UA1.4, UA3.1, UA4.2, UA4.5, UB1.2, UB1.4, UB3.1, UB4.2, UB4.5
IMONA: J5.7, UA4.1
IMONB: J5.9, UB4.1
TEMPA: J5.5, RTA.1
TEMPB: J5.11, RTB.1
TX1_CPL: DA1.1, RAF.1, RAT.1
TX1_D: CA2.1, CA6.1, CA7.1, CA90.1, CA91.1, CA92.1, CA93.1, UA1.3, UA3.2, UA4.6
TX1_DETV: CAD0.1, CAD2.1, DA1.2, RAD1.1, RAO.1
TX1_DI: CA1.2, UA1.1
TX1_IN: RAP1.1, RAP2.1
TX1_P: CA1.1, RAP2.2, RAP3.1
TX1_PA: CA3.1, CA80.1, CA81.1, CA82.1, CA83.1, RAS.1, RAV.2, UA4.4
TX2_CPL: DB1.1, RBF.1, RBT.1
TX2_D: CB2.1, CB6.1, CB7.1, CB90.1, CB91.1, CB92.1, CB93.1, UB1.3, UB3.2, UB4.6
TX2_DETV: CBD0.1, CBD2.1, DB1.2, RBD1.1, RBO.1
TX2_DI: CB1.2, UB1.1
TX2_IN: RBP1.1, RBP2.1
TX2_P: CB1.1, RBP2.2, RBP3.1
TX2_PA: CB3.1, CB80.1, CB81.1, CB82.1, CB83.1, RBS.1, RBV.2, UB4.4
V5A_I: CA5.1, RAV.1, UA3.3
V5B_I: CB5.1, RBV.1, UB3.3
V12: C1.1, C20.1, C21.1, C22.1, D6.1, Q3.2, R1.1, RAS.2, RBS.2, UA4.3, UB4.3
V12G: C1.2, D6.2, Q3.1, Q4.3, R1.2
VF: D5.1, F1.1, Q3.3, R2.1
VIN: F1.2, J1.1
